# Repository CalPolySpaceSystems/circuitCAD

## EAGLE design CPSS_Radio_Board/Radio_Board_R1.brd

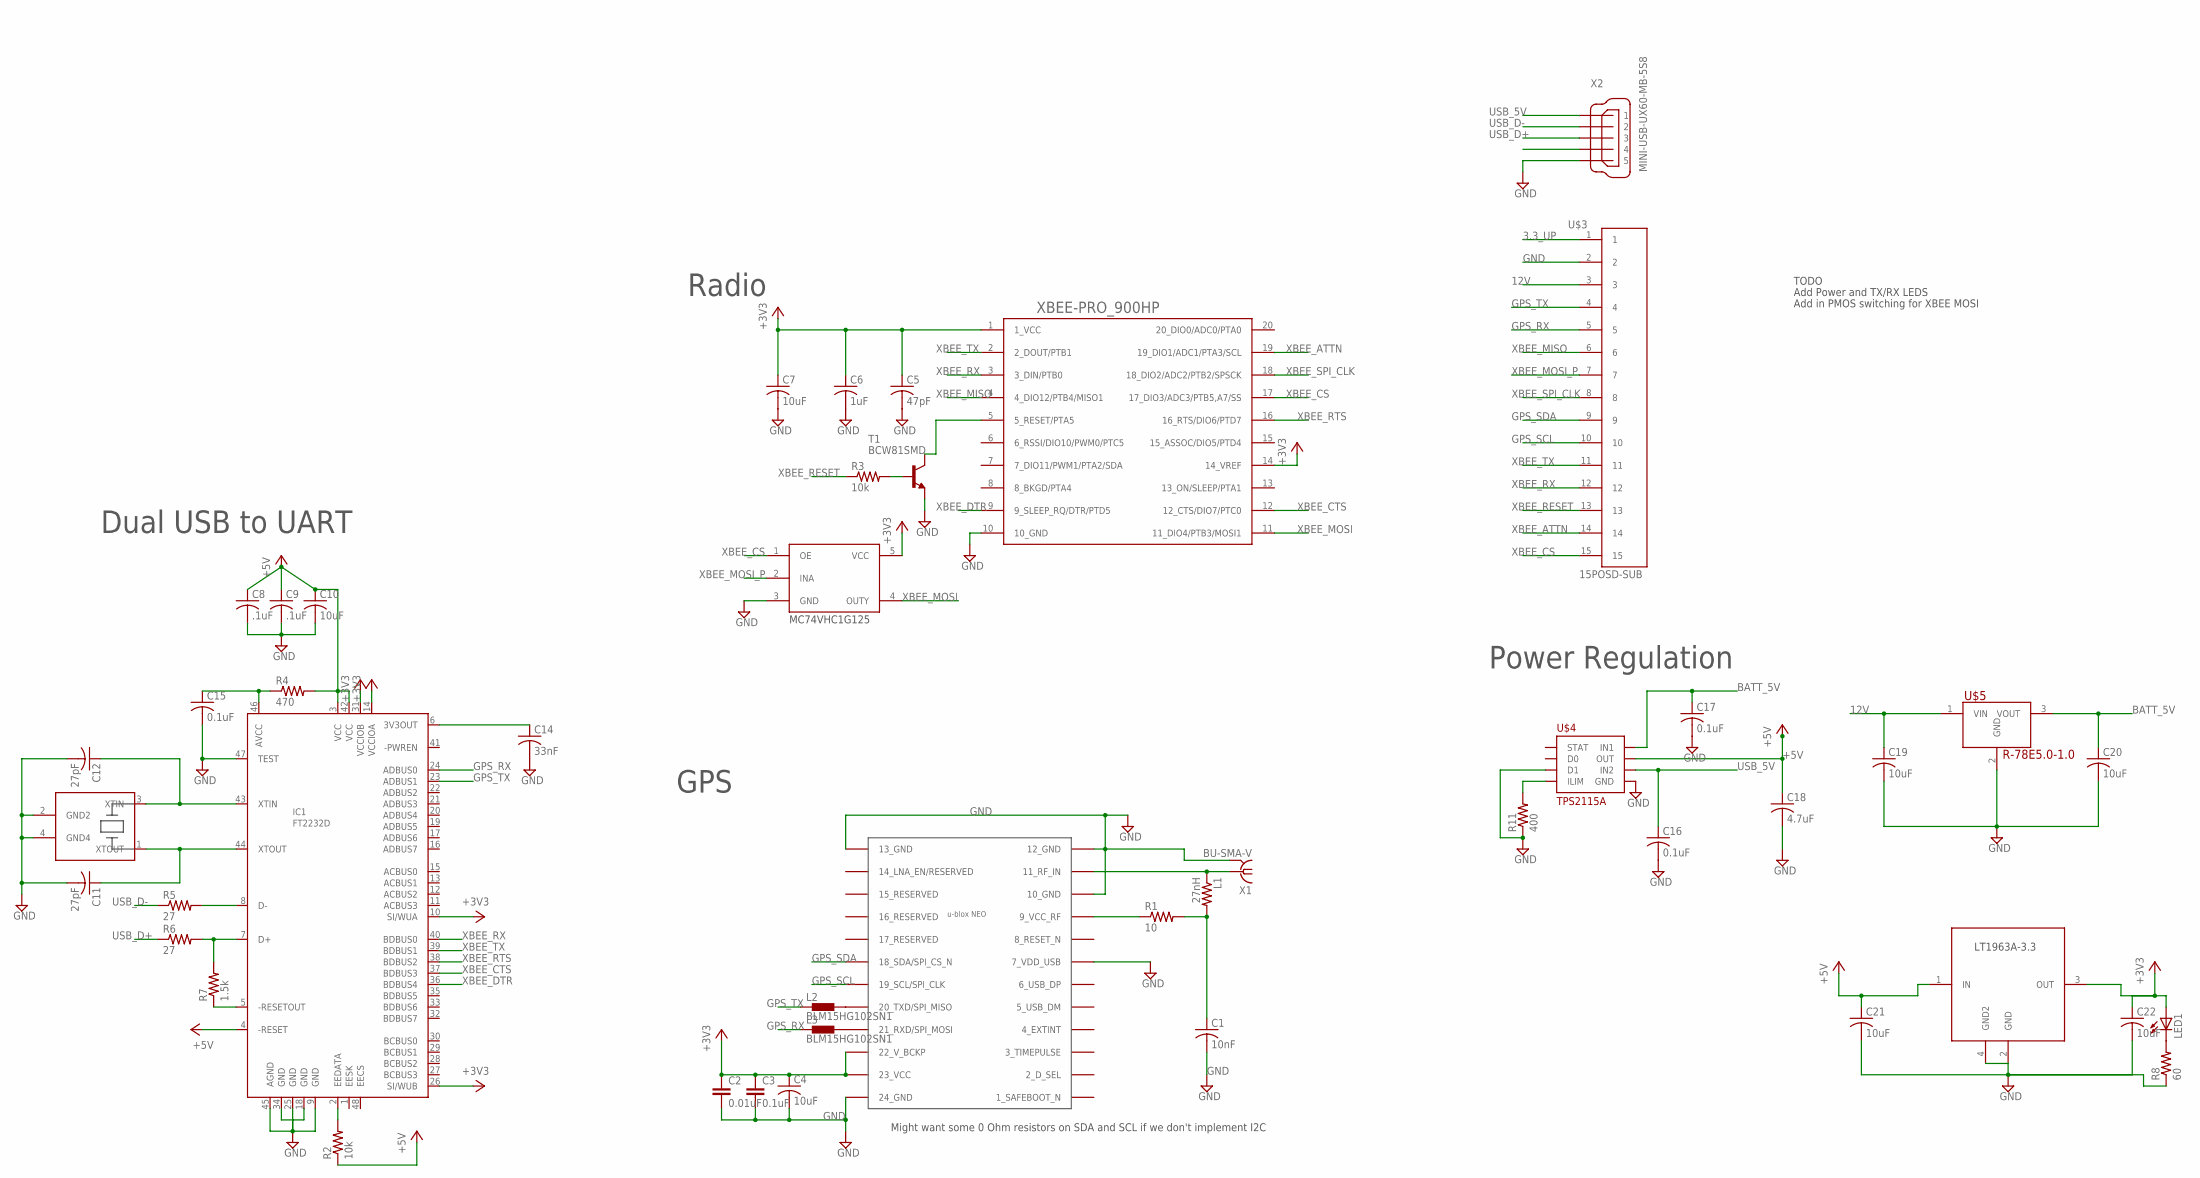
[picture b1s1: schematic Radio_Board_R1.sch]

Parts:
C1: 10nF; C0805
C2: 0.01uF; C0805
C3, C15, C16, C17: 0.1uF; C0805
C4, C19, C20, C21, C22: 10uF; C1206
C5: 47pF; C0805
C6: 1uF; C0805
C7, C10: 10uF; C0805
C8, C9: .1uF; C0805
C11, C12: 27pF; C0603
C14: 33nF; C0805
C18: 4.7uF; C1206
IC1: FT2232D; QFP48-7X7
L1: 27nH; R0805
L2, L3: BLM15HG102SN1; 0402
LED1: LED_E; LED_1206
R1: 10; R0805
R2, R3: 10k; R0805
R4: 470; R0805
R5, R6: 27; R0805
R7: 1.5k; M0805
R8: 60; R0805
R11: 400; R0805
T1: BCW81SMD; SOT23-BEC
U$1: NEO-M8
U$2: XBEE-PRO_900HP; XBEE_S3B
U$3: 15POSD-SUB
U$4: TPS2115A; TSSOP-8
U$5: R-78E5.0-1.0
U$6: MC74VHC1G125; SC70-5L
U$7: LT1963A-3.3; SOT223
U$8: ABBM-6; SMD-4_NOLEAD
X1: BU-SMA-V
X2: MINI-USB-UX60-MB-5S8; UX60-MB-5S8

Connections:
3.3_UP: U$3.1
12V: C19.1, U$3.3, U$5.1 (VIN)
+3V3: C2.1, C3.1, C4.1, C5.1, C6.1, C7.1, C22.1, IC1.10 (SI/WUA), IC1.14 (VCCIOA), IC1.26 (SI/WUB), IC1.31 (VCCIOB), LED1.A, U$1.22 (22_V_BCKP), U$1.23 (23_VCC), U$2.1 (1_VCC), U$2.14 (14_VREF), U$6.5 (VCC), U$7.3 (OUT)
+5V: C8.1, C9.1, C10.1, C18.1, C21.1, IC1.3 (VCC), IC1.4 (-RESET), IC1.42 (VCC), R2.1, R4.2, U$4.7 (OUT), U$7.1 (IN)
BATT_5V: C17.1, C20.1, U$4.8 (IN1), U$5.3 (VOUT)
GND: C1.2, C2.2, C3.2, C4.2, C5.2, C6.2, C7.2, C8.2, C9.2, C10.2, C11.2, C12.2, C14.2, C15.2, C16.2, C17.2, C18.2, C19.2, C20.2, C21.2, C22.2, IC1.9 (GND), IC1.18 (GND), IC1.25 (GND), IC1.34 (GND), IC1.45 (AGND), IC1.47 (TEST), R8.1, R11.1, T1.E, U$1.7 (7_VDD_USB), U$1.10 (10_GND), U$1.12 (12_GND), U$1.13 (13_GND), U$1.24 (24_GND), U$2.10 (10_GND), U$3.2, U$4.3 (D1), U$4.5 (GND), U$5.2 (GND), U$6.3 (GND), U$7.2 (GND), U$7.4 (GND2), U$8.2 (GND2), U$8.4 (GND4), X1.2, X1.3 (2), X1.4 (2), X1.5 (2), X2.5
GPS_RX: IC1.24 (ADBUS0), L3.1, U$3.5
GPS_SCL: U$1.19 (19_SCL/SPI_CLK), U$3.10
GPS_SDA: U$1.18 (18_SDA/SPI_CS_N), U$3.9
GPS_TX: IC1.23 (ADBUS1), L2.1, U$3.4
unnamed: C1.1, L1.2, R1.2
unnamed: R1.1, U$1.9 (9_VCC_RF)
unnamed: C12.1, IC1.43 (XTIN), U$8.3 (XTIN)
unnamed: C11.1, IC1.44 (XTOUT), U$8.1 (XTOUT)
unnamed: L1.1, U$1.11 (11_RF_IN), X1.1
unnamed: L2.2, U$1.20 (20_TXD/SPI_MISO)
unnamed: L3.2, U$1.21 (21_RXD/SPI_MOSI)
unnamed: C15.1, IC1.46 (AVCC), R4.1
unnamed: IC1.8 (D-), R5.2
unnamed: T1.C, U$2.5 (5_RESET/PTA5)
unnamed: R3.2, T1.B
unnamed: IC1.7 (D+), R6.2, R7.2
unnamed: LED1.C, R8.2
unnamed: IC1.2 (EEDATA), R2.2
unnamed: C14.1, IC1.6 (3V3OUT)
unnamed: IC1.5 (-RESETOUT), R7.1
unnamed: R11.2, U$4.4 (ILIM)
USB_5V: C16.1, U$4.6 (IN2), X2.1
USB_D+: R6.1, X2.3
USB_D-: R5.1, X2.2
XBEE_ATTN: U$2.19 (19_DIO1/ADC1/PTA3/SCL), U$3.14
XBEE_CS: U$2.17 (17_DIO3/ADC3/PTB5,A7/SS), U$3.15, U$6.1 (OE)
XBEE_CTS: IC1.37 (BDBUS3), U$2.12 (12_CTS/DIO7/PTC0)
XBEE_DTR: IC1.36 (BDBUS4), U$2.9 (9_SLEEP_RQ/DTR/PTD5)
XBEE_MISO: U$2.4 (4_DIO12/PTB4/MISO1), U$3.6
XBEE_MOSI: U$2.11 (11_DIO4/PTB3/MOSI1), U$6.4 (OUTY)
XBEE_MOSI_P: U$3.7, U$6.2 (INA)
XBEE_RESET: R3.1, U$3.13
XBEE_RTS: IC1.38 (BDBUS2), U$2.16 (16_RTS/DIO6/PTD7)
XBEE_RX: IC1.40 (BDBUS0), U$2.3 (3_DIN/PTB0), U$3.12
XBEE_SPI_CLK: U$2.18 (18_DIO2/ADC2/PTB2/SPSCK), U$3.8
XBEE_TX: IC1.39 (BDBUS1), U$2.2 (2_DOUT/PTB1), U$3.11

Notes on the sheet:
Might want some 0 Ohm resistors on SDA and SCL if we don't implement I2C
Power Regulation
Radio
Dual USB to UART
GPS
TODO
Add Power and TX/RX LEDS
Add in PMOS switching for XBEE MOSI

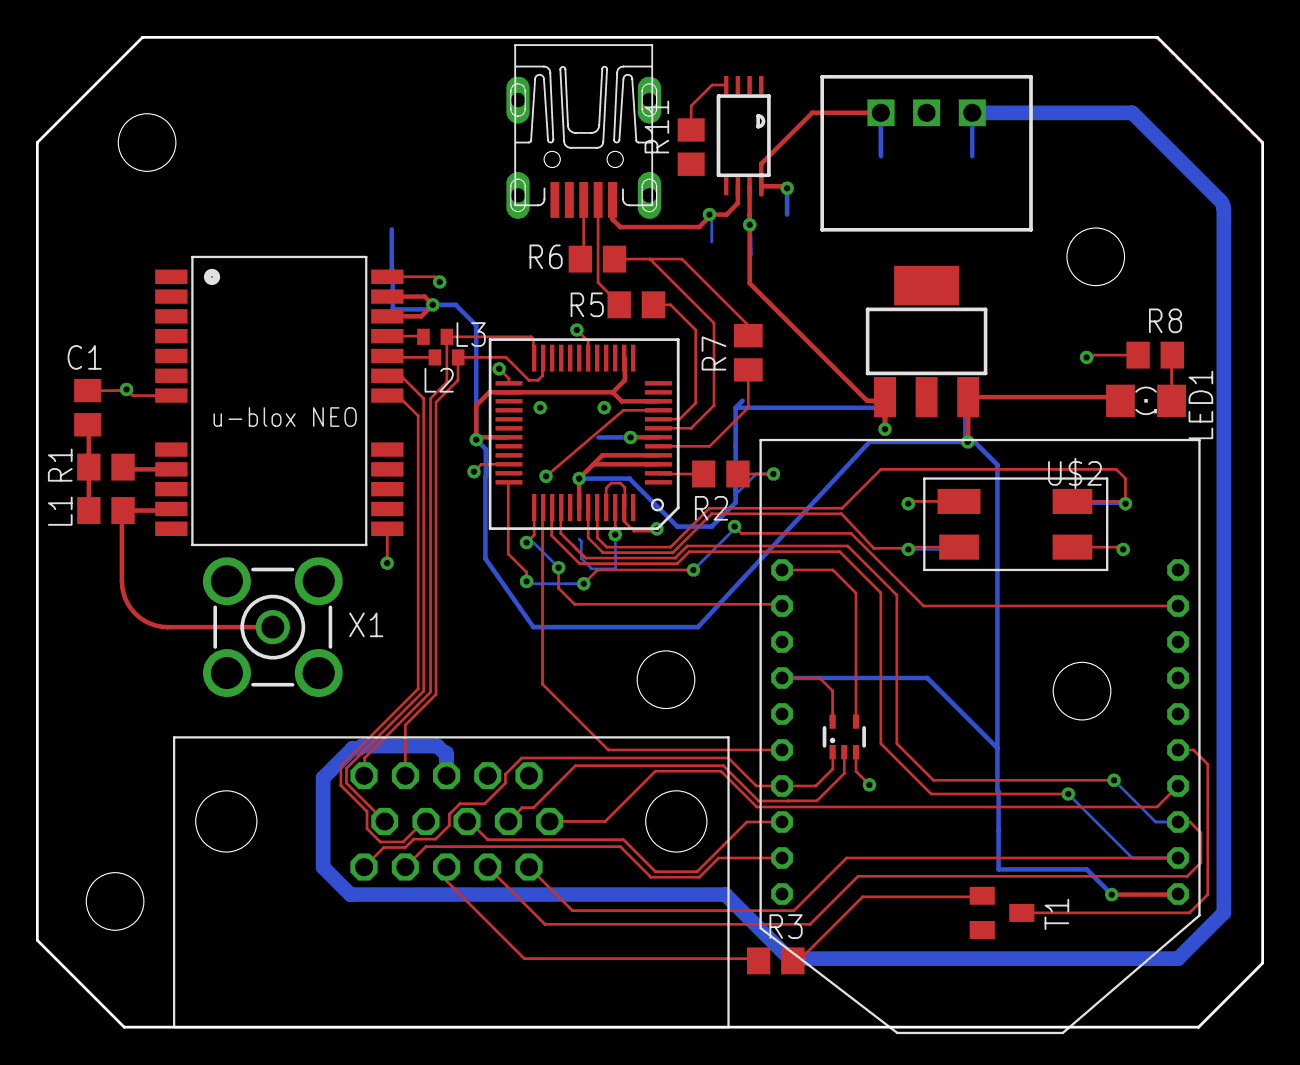
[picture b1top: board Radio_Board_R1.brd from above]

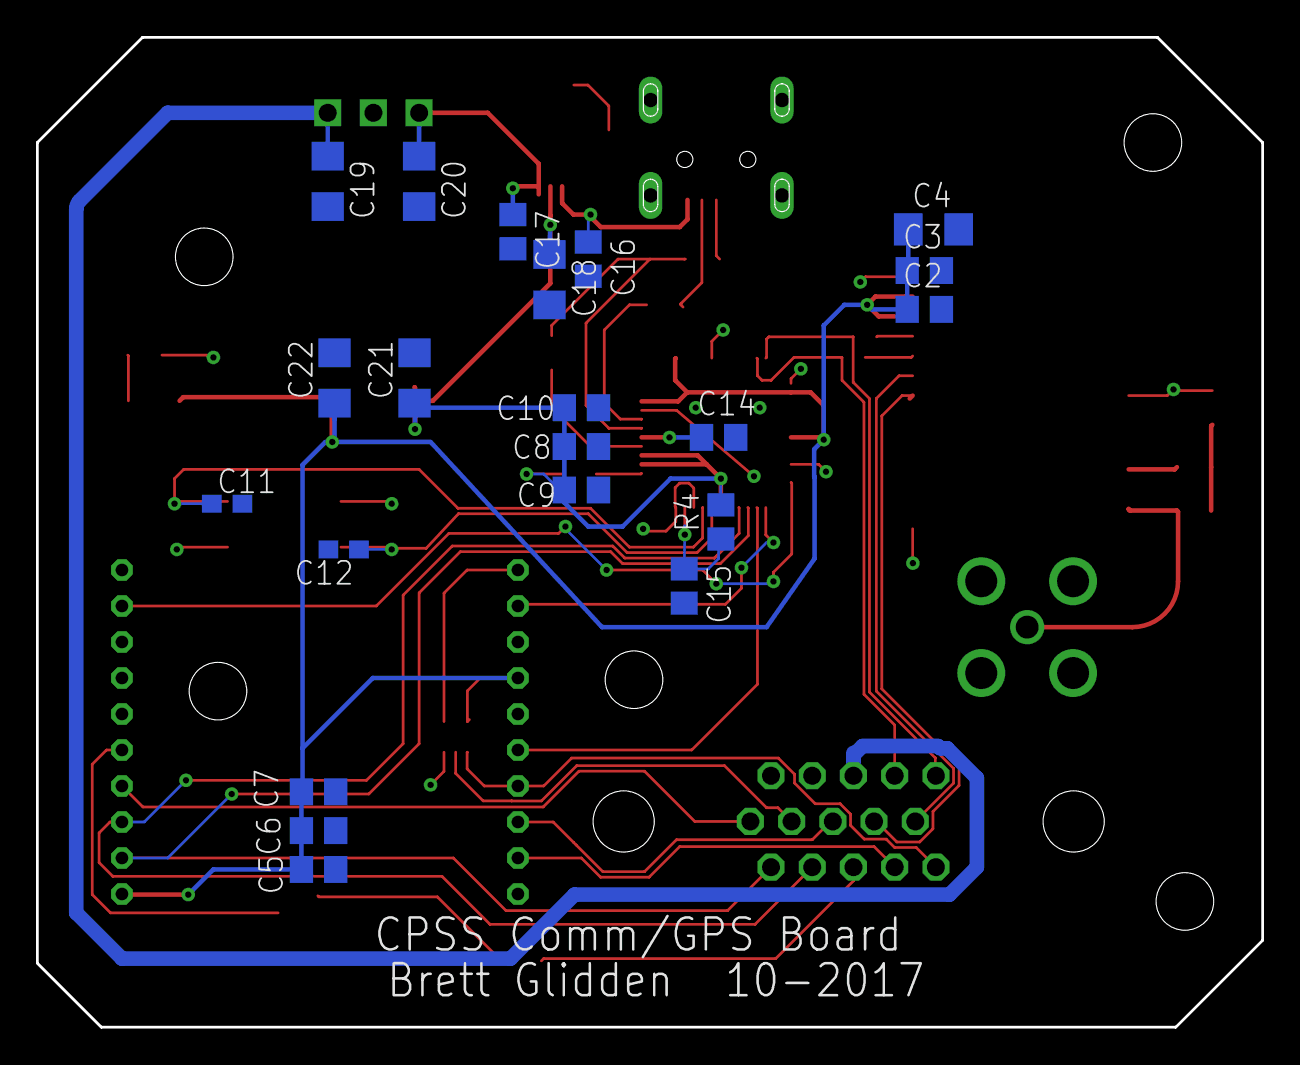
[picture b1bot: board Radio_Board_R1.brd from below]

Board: 2 copper layers, 68.1 x 55.0 mm, 46 parts (21 on the bottom side), 41 nets.

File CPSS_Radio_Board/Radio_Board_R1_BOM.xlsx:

Part | list exported | from D:/Documents/eagle/CPSS | _Radio_Board/ | Radio_Board_R1.sch | at 10/22/2017 8:39 AM
Qty | Value | Device | Package | Parts | Description | Digikey | Mouser
1 |  | LED_E | LED_1206 | LED1 | LED | 404-1046-1-ND
2 | .1uF | C-USC0805 | C0805 | C8, C9 | CAPACITOR, American symbol | 399-1170-1-ND
1 | 0.01uF | C | C0805 | C2 | CAPACITOR, European symbol | 399-1158-1-ND
1 | 0.1uF | C | C0805 | C3 | CAPACITOR, European symbol | 399-1170-1-ND
3 | 0.1uF | C-USC0805 | C0805 | C15, C16, C17 | CAPACITOR, American symbol | 399-1170-1-ND
1 | 1.5k | R-US_M0805 | M0805 | R7 | RESISTOR, American symbol | 311-1.50KCRCT-ND
1 | 10 | R-US_R0805 | R0805 | R1 | RESISTOR, American symbol | 311-10.0CRCT-ND
2 | 10k | R-US_R0805 | R0805 | R2, R3 | RESISTOR, American symbol | 311-10KARCT-ND
1 | 10nF | C-USC0805 | C0805 | C1 | CAPACITOR, American symbol | 399-1158-1-ND
2 | 10uF | C-USC0805 | C0805 | C7, C10 | CAPACITOR, American symbol | 478-8115-1-ND
5 | 10uF | C-USC1206 | C1206 | C4, C19, C20, C21, |  | 478-8151-1-ND
1 | 15POSD-SUB | 15POSD-SUB | 15POSD-SUB | U$3 |  | A35118-ND
1 | 1uF | C-USC0805 | C0805 | C6 | CAPACITOR, American symbol | 490-1691-1-ND
2 | 27 | R-US_R0805 | R0805 | R5, R6 | RESISTOR, American symbol | 311-27.0CRCT-ND
1 | 27nH | R-US_R0805 | R0805 | L1 | RESISTOR, American symbol | 490-16032-1-ND
2 | 27pF | C-USC0603 | C0603 | C11, C12 | CAPACITOR, American symbol | 709-1173-1-ND
1 | 33nF | C-USC0805 | C0805 | C14 | CAPACITOR, American symbol | 445-6950-1-ND
1 | 4.7uF | C-USC1206 | C1206 | C18 | CAPACITOR, American symbol | 478-8265-1-ND
1 | 400 | R-US_R0805 | R0805 | R11 | RESISTOR, American symbol | 311-402CRCT-ND
1 | 470 | R-US_R0805 | R0805 | R4 | RESISTOR, American symbol | 311-470CRCT-ND
1 | 47pF | C-USC0805 | C0805 | C5 | CAPACITOR, American symbol | 490-3612-1-ND
1 | 60 | R-US_R0805 | R0805 | R8 | RESISTOR, American symbol | 311-59.0CRCT-ND
1 | ABBM-6 | ABBM-6 | SMD-4_NOLEAD | U$8 |  | 535-10156-1-ND
1 | BCW81SMD | BCW81SMD | SOT23-BEC | T1 | NPN Transistor | MMBT2222ALT1GOSCT-ND
2 | BLM15HG102SN1 | BLM15HG102SN1 | 402 | L2, L3 | EMIFIL (R) Chip Ferrite Bead for GHz Noise | 490-4003-1-ND
1 | BU-SMA-V | BU-SMA-V | BU-SMA-V | X1 | FEMALE SMA CONNECTOR
1 | FT2232D | FT2232D | QFP48-7X7 | IC1 | FT2232 DUAL USB UART/FIFO (4th Gen USB 2 full speed) | 768-1010-1-ND
1 | LT1963A-3.3 | LT1963A-3.3 | SOT223 | U$7 |  | LT1963AEST-3.3#TRPBFCT-ND
1 | MC74VHC1G125 | MC74VHC1G125 | SC70-5L | U$6 |  |  | 863-M74VHC1G125DFT1G
1 | MINI-USB-UX60 | -MB-5S8 MINI-USB-UX60-MB-5S8 | UX60-MB-5S8 | X2 | MINI USB Connector | H2960CT-ND
1 | NEO-M8 | NEO-M8 | NEO-M8 | U$1 | u-blox NEO GNSS module | 672-1008-1-ND
1 | R-78E5.0-1.0 | R-78E5.0-1.0 | R-78E5.0-1.0 | U$5 |  | 945-2201-ND
1 | TPS2115A | TPS2115A | TSSOP-8 | U$4 |  |  | 595-TPS2115APWR
1 | XBEE-PRO_900H | P XBEE-PRO_900HP | XBEE_S3B | U$2 |  | 602-1299-ND

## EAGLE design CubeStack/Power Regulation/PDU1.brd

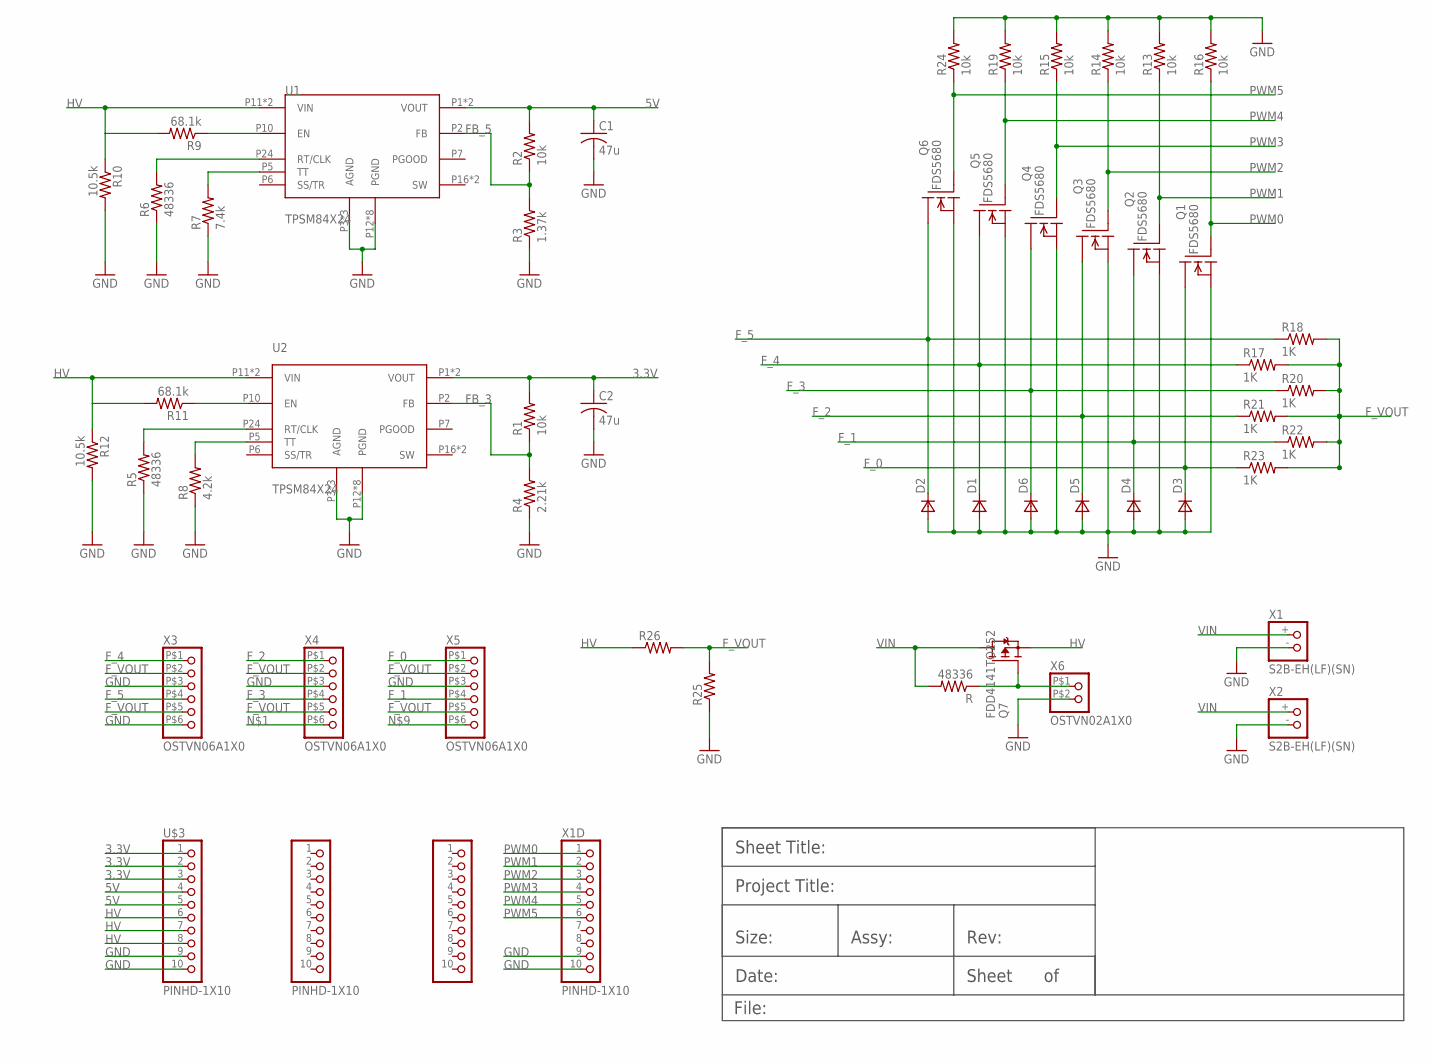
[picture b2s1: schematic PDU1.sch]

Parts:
C1, C2: 47u; C1206
D1, D2, D3, D4, D5, D6: DSOD323; SOD323
Q1, Q2, Q3, Q4, Q5, Q6: FDS5680; SO-8
Q7: FDD4141TO252; TO252
R, R5, R6: 48336; R1206
R1, R2: 10k; R1206
R3: 1.37k; R1206
R4: 2.21k; R1206
R7: 7.4k; R1206
R8: 4.2k; R1206
R9, R11: 68.1k; R1206
R10, R12: 10.5k; R1206
R13, R14, R15, R16, R19, R24: 10k; R0603
R17, R18, R20, R21, R22, R23: 1K; R0603
R25, R26: R-US_R6332; R6332
U1, U2: TPSM84X24; QFM-5.4
U$3, U$4, U$5: PINHD-1X10; 1X10-BIG
X1, X2: S2B-EH(LF)(SN); S2B-EH
X1D: PINHD-1X10; 1X10-BIG
X3, X4, X5: OSTVN06A1X0
X6: OSTVN02A1X0

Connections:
3.3V: C2.1, R1.2, U2.P1 (VOUT), U2.P8 (VOUT), U$3.1, U$3.2, U$3.3
5V: C1.1, R2.2, U1.P1 (VOUT), U1.P8 (VOUT), U$3.4, U$3.5
EN: Q7.1 (G), R.1, X6.P$1 (1)
FB_3: R1.1, R4.2, U2.P2 (FB)
FB_5: R2.1, R3.2, U1.P2 (FB)
F_0: D3.1 (C), Q1.5 (D), Q1.6 (D), Q1.7 (D), Q1.8 (D), R23.1, X5.P$1 (1)
F_1: D4.1 (C), Q2.5 (D), Q2.6 (D), Q2.7 (D), Q2.8 (D), R22.1, X5.P$4 (4)
F_2: D5.1 (C), Q3.5 (D), Q3.6 (D), Q3.7 (D), Q3.8 (D), R21.1, X4.P$1 (1)
F_3: D6.1 (C), Q4.5 (D), Q4.6 (D), Q4.7 (D), Q4.8 (D), R20.1, X4.P$4 (4)
F_4: D1.1 (C), Q5.5 (D), Q5.6 (D), Q5.7 (D), Q5.8 (D), R17.1, X3.P$1 (1)
F_5: D2.1 (C), Q6.5 (D), Q6.6 (D), Q6.7 (D), Q6.8 (D), R18.1, X3.P$4 (4)
F_VOUT: R17.2, R18.2, R20.2, R21.2, R22.2, R23.2, R25.2, R26.2, X3.P$2 (2), X3.P$5 (5), X4.P$2 (2), X4.P$5 (5), X5.P$2 (2), X5.P$5 (5)
GND: C1.2, C2.2, D1.2 (A), D2.2 (A), D3.2 (A), D4.2 (A), D5.2 (A), D6.2 (A), Q1.1 (S), Q1.2 (S), Q1.3 (S), Q2.1 (S), Q2.2 (S), Q2.3 (S), Q3.1 (S), Q3.2 (S), Q3.3 (S), Q4.1 (S), Q4.2 (S), Q4.3 (S), Q5.1 (S), Q5.2 (S), Q5.3 (S), Q6.1 (S), Q6.2 (S), Q6.3 (S), R3.1, R4.1, R5.1, R6.1, R7.1, R8.1, R10.2, R12.2, R13.2, R14.2, R15.2, R16.2, R19.2, R24.2, R25.1, U1.P3 (AGND), U1.P9 (AGND), U1.P12 (PGND), U1.P13 (PGND), U1.P14 (PGND), U1.P15 (PGND), U1.P18 (PGND), U1.P19 (PGND), U1.P20 (PGND), U1.P21 (PGND), U1.P23 (AGND), U2.P3 (AGND), U2.P9 (AGND), U2.P12 (PGND), U2.P13 (PGND), U2.P14 (PGND), U2.P15 (PGND), U2.P18 (PGND), U2.P19 (PGND), U2.P20 (PGND), U2.P21 (PGND), U2.P23 (AGND), U$3.9, U$3.10, X1.- (2), X1D.9, X1D.10, X2.- (2), X3.P$3 (3), X3.P$6 (6), X4.P$3 (3), X5.P$3 (3), X6.P$2 (2)
HV: Q7.2 (S), R9.2, R10.1, R11.2, R12.1, R26.1, U1.P11 (VIN), U1.P22 (VIN), U2.P11 (VIN), U2.P22 (VIN), U$3.6, U$3.7, U$3.8
unnamed: R6.2, U1.P24 (RT/CLK)
unnamed: R8.2, U2.P5 (TT)
unnamed: R5.2, U2.P24 (RT/CLK)
unnamed: R7.2, U1.P5 (TT)
unnamed: R9.1, U1.P10 (EN)
unnamed: R11.1, U2.P10 (EN)
PWM0: Q1.4 (G), R16.1, X1D.1
PWM1: Q2.4 (G), R13.1, X1D.2
PWM2: Q3.4 (G), R14.1, X1D.3
PWM3: Q4.4 (G), R15.1, X1D.4
PWM4: Q5.4 (G), R19.1, X1D.5
PWM5: Q6.4 (G), R24.1, X1D.6
VIN: Q7.3 (D), R.2, X1.+ (1), X2.+ (1)

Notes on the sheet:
C:/Users/patri/Pictures/CPSSLOGO.bmp

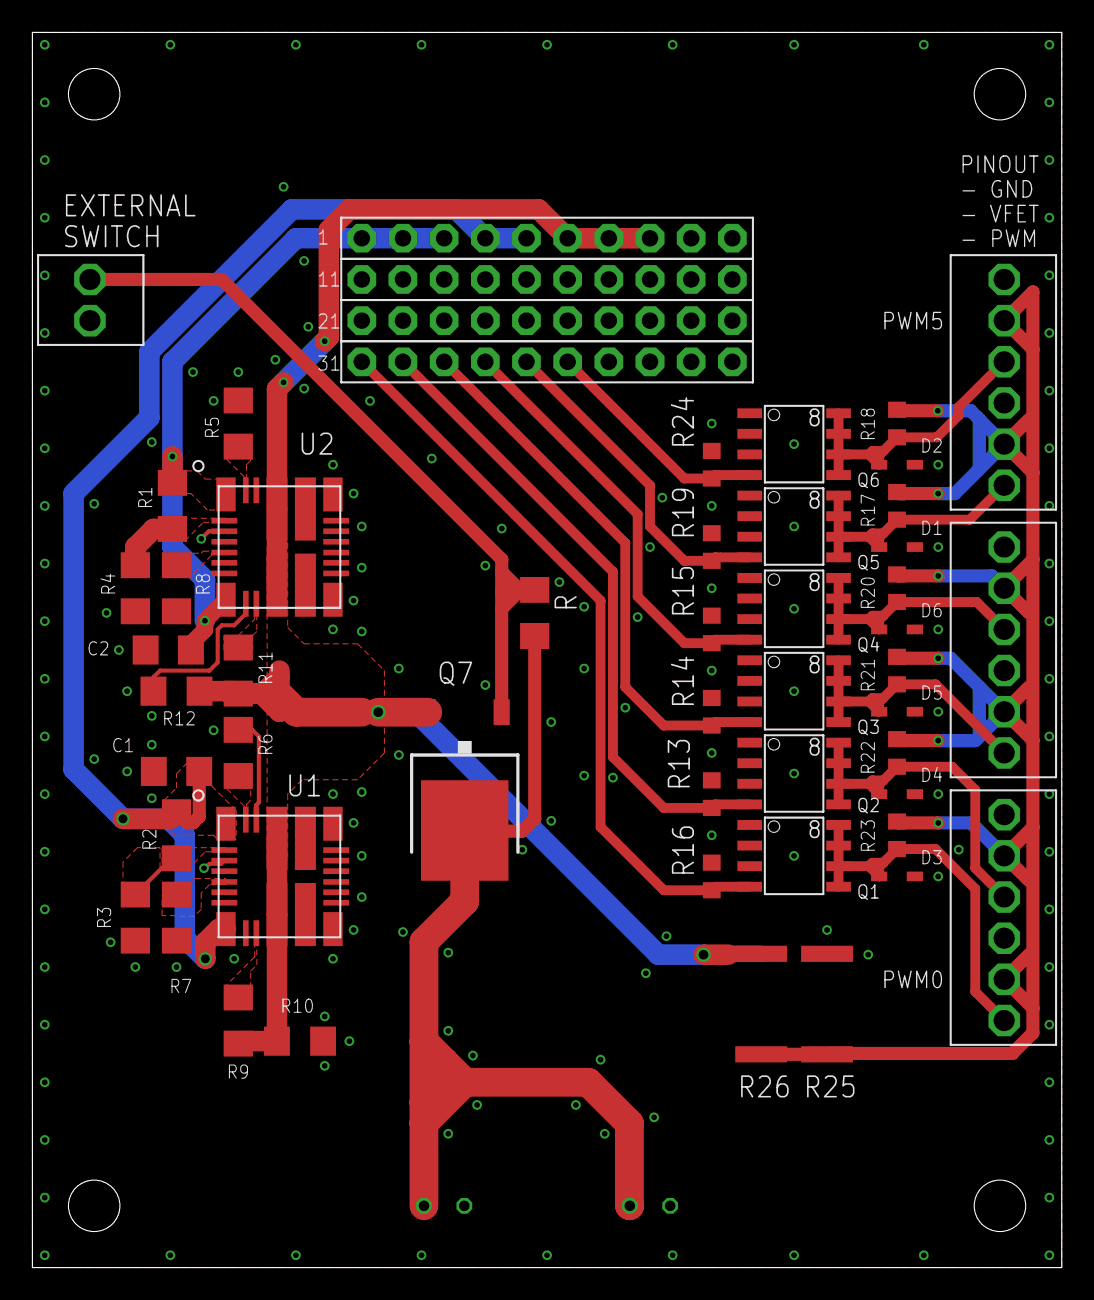
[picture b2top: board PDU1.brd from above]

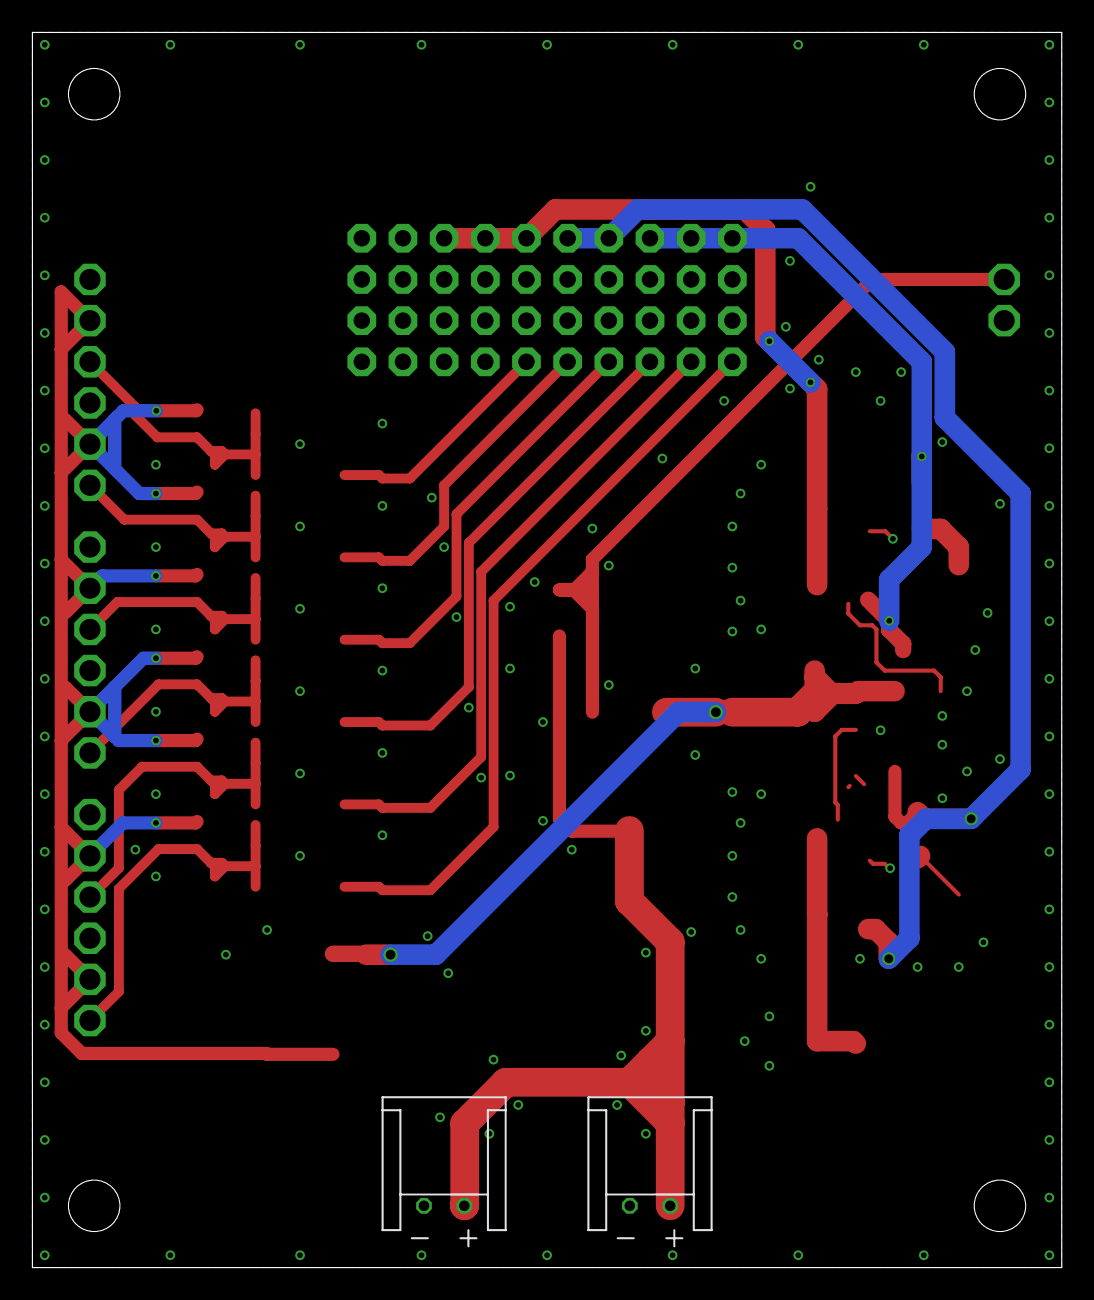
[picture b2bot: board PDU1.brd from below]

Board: 2 copper layers, 63.5 x 76.2 mm, 54 parts (2 on the bottom side), 27 nets.

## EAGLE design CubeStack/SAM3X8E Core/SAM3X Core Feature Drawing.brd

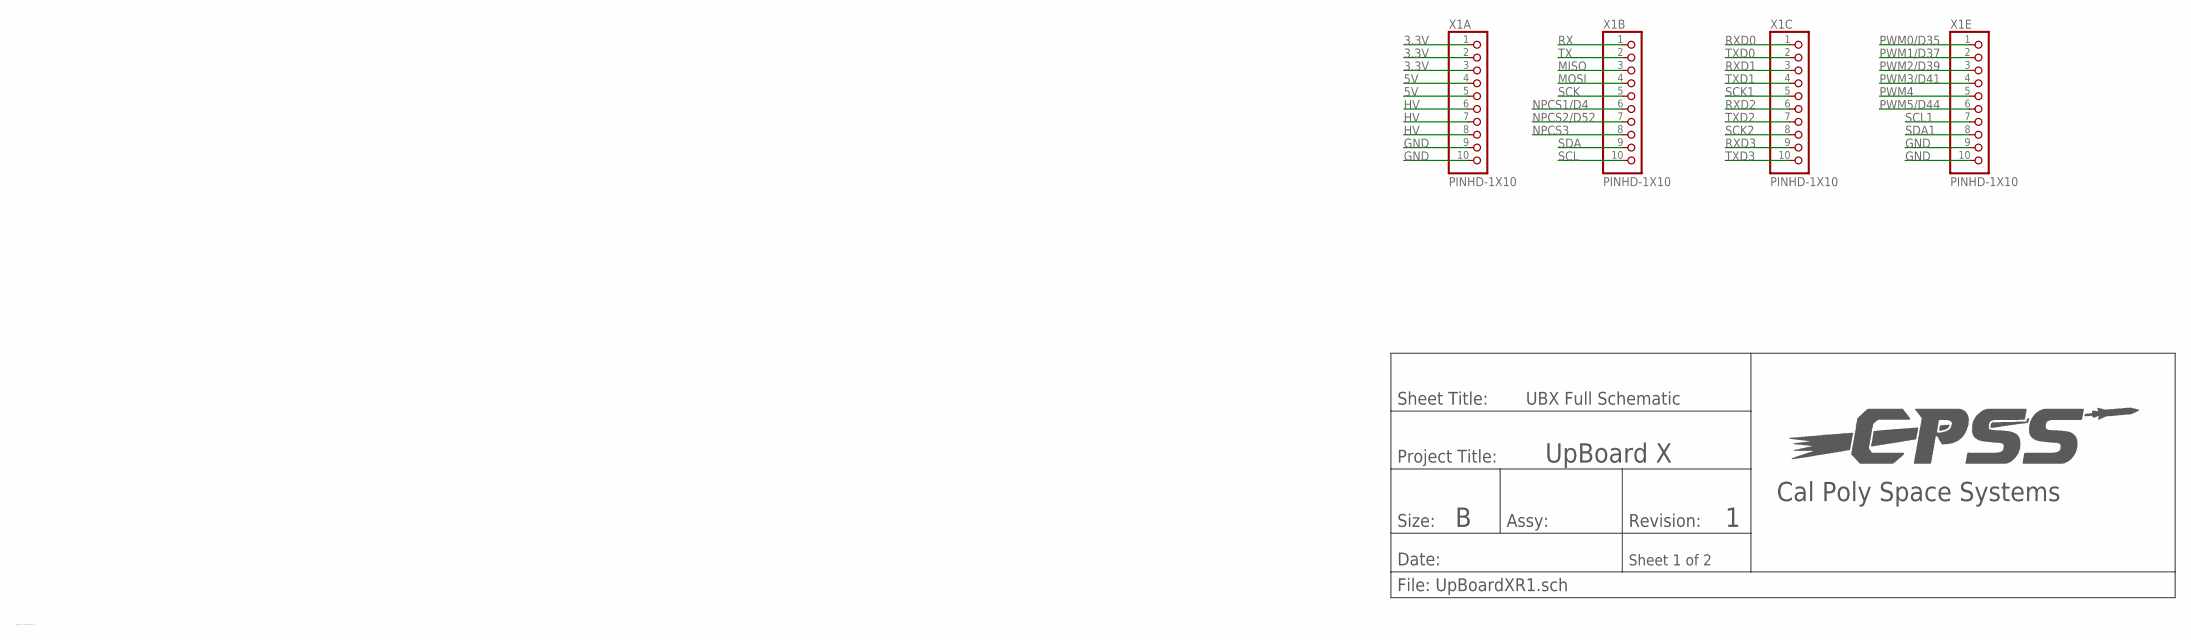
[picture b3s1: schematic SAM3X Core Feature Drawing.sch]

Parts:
X1A, X1B, X1C, X1E: PINHD-1X10; 1X10-BIG

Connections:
3.3V: X1A.1, X1A.2, X1A.3
5V: X1A.4, X1A.5
GND: X1A.9, X1A.10, X1E.9, X1E.10
HV: X1A.6, X1A.7, X1A.8
MISO: X1B.3
MOSI: X1B.4
NPCS1/D4: X1B.6
NPCS2/D52: X1B.7
NPCS3: X1B.8
PWM0/D35: X1E.1
PWM1/D37: X1E.2
PWM2/D39: X1E.3
PWM3/D41: X1E.4
PWM4: X1E.5
PWM5/D44: X1E.6
RX: X1B.1
RXD0: X1C.1
RXD1: X1C.3
RXD2: X1C.6
RXD3: X1C.9
SCK: X1B.5
SCK1: X1C.5
SCK2: X1C.8
SCL: X1B.10
SCL1: X1E.7
SDA: X1B.9
SDA1: X1E.8
TX: X1B.2
TXD0: X1C.2
TXD1: X1C.4
TXD2: X1C.7
TXD3: X1C.10

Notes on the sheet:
Assy:
Size:
Revision:
Sheet 1 of 2
Date:
Sheet Title:
Project Title:
File: UpBoardXR1.sch
UBX Full Schematic
UpBoard X
C:/Users/Patrick Chizek/Pictures/CPSSLOGO.bmp
Cal Poly Space Systems

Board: 2 copper layers, 4 parts (0 on the bottom side), 4 nets, no tracks yet.

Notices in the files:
parts and their libraries:
pimoroni: Licensing: CC v3.0 Share-Alike You are welcome to use this library for commercial purposes.
